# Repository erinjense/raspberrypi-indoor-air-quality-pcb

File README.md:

# zephyrus-iaq
Hardware and Software for an Indoor Air Quality Logger

More to come...

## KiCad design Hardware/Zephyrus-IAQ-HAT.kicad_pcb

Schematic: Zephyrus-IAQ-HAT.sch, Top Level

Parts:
J1: Conn_02x20_Odd_Even__Rpi; PinSocket_2x20_P2.54mm_Vertical
J2: USART; JST_SM04B-SRSS-TB(LF)(SN)
R9, R20: 10k; R_0805_2012Metric
U3: BSS138

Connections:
+3V3: J1.1, J1.17, R20.1, U3.G; also elsewhere on the board
+5V: J2.4 (VCC), R9.1; also elsewhere on the board
/FAN_PWM1: J1.33; also elsewhere on the board
/FAN_nSLEEP: J1.22; also elsewhere on the board
/GPIO2(SDA1): J1.3; also elsewhere on the board
/GPIO3(SCL1): J1.5; also elsewhere on the board
/GPIO4(GCLK): J1.7
/GPIO5: J1.29
/GPIO6: J1.31
/GPIO7(SPI1_CE_N): J1.26
/GPIO8(SPI0_CE_N): J1.24
/GPIO9(SPI0_MISO): J1.21
/GPIO10(SPI0_MOSI): J1.19
/GPIO11(SPI0_SCK): J1.23
/GPIO12(PWM0): J1.32
/GPIO14(TXD0): J1.8, J2.1 (TX)
/GPIO15(RXD0): J1.10, R20.2, U3.S
/GPIO16: J1.36
/GPIO17(GEN0): J1.11; also elsewhere on the board
/GPIO18(GEN1)(PWM0): J1.12; also elsewhere on the board
/GPIO19(SPI1_MISO): J1.35
/GPIO20(SPI1_MOSI): J1.38
/GPIO21(SPI1_SCK): J1.40
/GPIO22(GEN3): J1.15; also elsewhere on the board
/GPIO23(GEN4): J1.16
/GPIO24(GEN5): J1.18
/GPIO26: J1.37
/GPIO27(GEN2): J1.13; also elsewhere on the board
/ID_SC_EEPROM: J1.28; also elsewhere on the board
/ID_SD_EEPROM: J1.27; also elsewhere on the board
/RXD0: J2.2 (RX), R9.2, U3.D
GND: J1.6, J1.9, J1.14, J1.20, J1.25, J1.30, J1.34, J1.39, J2.3 (GND); also elsewhere on the board

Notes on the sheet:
Power Mgmt.
DAC/Buffer power control for Analog Sensors Analog Sensor Ports: A0-A5
A0 - A5: Analog Channels Buffers (250 [mA] to A0 - A5) DAC (0 - 5 [V] to Buffers)
Unidirectional Fan
6:1 Multiplexed ADC (0 - 5 [V])
3.3V to 5V I2C I2C Connectors
Multiplexed 16-bit ADC
I2C Connectors and I2C Logic Level Conversion
Software Driver: zephyrus-iaq/Software/HAT/IAQ_DAC43608.py zephyrus-iaq/Software/HAT/IAQ_AnalogPortController.py
Software Driver: zephyrus-iaq/Software/HAT/IAQ_Mux.py zephyrus-iaq/Software/third_party/Adafruit_I2C.py zephyrus-iaq/Software/third_party/Adafruit_ADS1x15.py
Raspberry Pi Header
5V USART , 3.3V Pi Compatible
Raspberry Pi HAT Requirements: EEPROM
Mnt. Holes
EEPROM
SCL/SDA 5V is on the same I2C bus as 3.3V SCL/SDA
Step the TX line from target device down for 3.3V RX on Raspbery line Similiar BSS138 circuit as I2C logic level shifting.
Raspberry Pi 3.3V TX can register HIGH on 5V TTL compatible USART
PWM controlled Fan

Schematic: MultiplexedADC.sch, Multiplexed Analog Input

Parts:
C11, C12, C14: 100nF; C_0805_2012Metric
J9: Alert; PinHeader_1x01_P2.54mm_Vertical
R10: 10K; R_0805_2012Metric
U6: MUX; SOP65P640X120-16N
U7: ADC; SOP50P490X110-10N
U8: V-Shift; SOP65P640X120-14N

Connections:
+5V: C11.1, C12.1, C14.1, R10.1, U6.16 (VCC), U7.8 (VDD), U8.14 (VCC); also elsewhere on the board
/ADC0: U6.13 (Y0); also elsewhere on the board
/ADC1: U6.14 (Y1); also elsewhere on the board
/ADC2: U6.15 (Y2); also elsewhere on the board
/ADC3: U6.12 (Y3); also elsewhere on the board
/ADC4: U6.1 (Y4); also elsewhere on the board
/ADC5: U6.5 (Y5); also elsewhere on the board
/GPIO17(GEN0): U8.2 (1A); also elsewhere on the board
/GPIO22(GEN3): U8.9 (3A); also elsewhere on the board
/GPIO27(GEN2): U8.5 (2A); also elsewhere on the board
/Multiplexed ADC/MUL_A_5V: U6.11 (A), U8.3 (1Y)
/Multiplexed ADC/MUL_B_5V: U6.10 (B), U8.6 (2Y)
/Multiplexed ADC/MUL_C_5V: U6.9 (C), U8.8 (3Y)
/SCL_5: U7.1 (ADDR), U7.10 (SCL); also elsewhere on the board
/SDA_5: U7.9 (SDA); also elsewhere on the board
GND: C11.2, C12.2, C14.2, U6.6 (~INH~), U6.7 (GND), U6.8 (GND), U7.3 (GND), U7.5 (AIN1), U7.6 (AIN2), U7.7 (AIN3), U8.1 (1!OE), U8.4 (2!OE), U8.7 (GND), U8.10 (3!OE); also elsewhere on the board
unnamed: J9.1, R10.2, U7.2 (ALERT/RDY)
unnamed: U6.3 (COM), U7.4 (AIN0)

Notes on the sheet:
Multiplexer 6:1 Analog Input to ADC Channels: A0 - A5
ADS1115 16-bit ADC 5 [V] I2C Interface
Software Driver: zephyrus-iaq/Software/third_party/Adafruit_I2C.py zephyrus-iaq/Software/third_party/Adafruit_ADS1x15.py
Software Driver: zephyrus-iaq/Software/HAT/IAQ_Mux.py
Raspberry Pi 3.3 [V] TTL Shifted To Multiplexer 5 [V] CMOS.
Address: 0x4B

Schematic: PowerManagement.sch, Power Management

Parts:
C1, C13: 47uF; C_0805_2012Metric
D1: PWR; D_0805_2012Metric
D10: SMBJ5.0A
F1: MF-MSMF250/X; Fuse_1812_4532Metric
J7: 10103594-0001LF; FCI_10103594-0001LF
R3: 330; R_0805_2012Metric
R4: 2.61k; R_0805_2012Metric
R23: 100k; R_0805_2012Metric
R24: 287; R_0805_2012Metric
U10: 5V; REG_EY1501DI-ADJ

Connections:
+5V: C13.1, R4.1, R23.1, U10.1 (Vout), U10.2 (Vout); also elsewhere on the board
/Power Management/VREG_SENSE: R4.2, R24.1, U10.3 (SENSE)
GND: C1.2, C13.2, D10.2, J7.5, R3.2, R23.2, R24.2, U10.4 (PG), U10.5 (GND), U10.11 (Pad); also elsewhere on the board
unnamed: C1.1, D1.2 (A), D10.1, F1.2, U10.7 (ENABLE), U10.9 (Vin), U10.10 (Vin)
unnamed: D1.1 (K), R3.1
unnamed: F1.1, J7.1

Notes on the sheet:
5V Power: Micro USB Input
5V Regulator (0.125V drop @ 2A)
Polyfuse 2.5A hold ; 5A trip
TVS 5V Reverse 9.2V Clamp Max
The micro-USB power input was inspired by reading the documents on the Raspberry Pi 3 B+ at the following link (Upper Left Hand Corner of Schematic): https://www.raspberrypi.org/documentation/hardware/raspberrypi/schematics/rpi_SCH_3bplus_1p0_reduced.pdf License: https://www.raspberrypi.org/creativ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

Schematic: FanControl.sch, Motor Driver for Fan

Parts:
C3, C4: 100nF; C_0805_2012Metric
J4: Fan; SM02B-SRSS-TB(LF)(SN)
U2: Fan Driver; SON50P200X200X80-9N

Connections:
+3V3: C4.1, U2.8 (VCC); also elsewhere on the board
+5V: C3.1, U2.1 (VM); also elsewhere on the board
/FAN_PWM1: U2.6 (IN1); also elsewhere on the board
/FAN_nSLEEP: U2.7 (nSLEEP); also elsewhere on the board
GND: C3.2, C4.2, U2.4 (GND), U2.5 (IN2), U2.9 (Thermal); also elsewhere on the board
unnamed: J4.1, U2.2 (OUT1)
unnamed: J4.2, U2.3 (OUT2)

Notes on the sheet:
2-Pin Connector for Fan (Unidirectional Control)

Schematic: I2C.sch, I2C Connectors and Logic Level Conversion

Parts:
J6, J8: I2C 3.3V; JST_SM04B-SRSS-TB(LF)(SN)
J16: I2C 5V; JST_SM04B-SRSS-TB(LF)(SN)
J17: PPS; PinSocket_1x01_P2.54mm_Vertical
R16, R17: 10k; R_0805_2012Metric
U4, U5: BSS138

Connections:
+3V3: J6.2 (VDD), J8.2 (VDD), U4.G, U5.G; also elsewhere on the board
+5V: J16.2 (VDD), R16.1, R17.1; also elsewhere on the board
/GPIO2(SDA1): J6.3 (SDA), J8.3 (SDA), U4.S; also elsewhere on the board
/GPIO3(SCL1): J6.4 (SCL), J8.4 (SCL), U5.S; also elsewhere on the board
/GPIO18(GEN1)(PWM0): J17.1; also elsewhere on the board
/SCL_5: J16.4 (SCL), R17.2, U5.D; also elsewhere on the board
/SDA_5: J16.3 (SDA), R16.2, U4.D; also elsewhere on the board
GND: J6.1 (GND), J8.1 (GND), J16.1 (GND); also elsewhere on the board

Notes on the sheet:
3.3V I2C Connectors Compatible with Sparkfun's Qwiic system.
Pulse Per Second Breakout for Sparkfun GPS
3.3V and 5V I2C Connectors
The Bi-Directional logic level shift using the BSS138 was inspired by reading Sparkfun's schematic https://cdn.sparkfun.com/datasheets/BreakoutBoards/Logic_Level_Bidirectional.pdf License: https://creativecommons.org/licenses/by-sa/3.0/us/ Changes: There is no Pull-Up on the Source, because of the 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

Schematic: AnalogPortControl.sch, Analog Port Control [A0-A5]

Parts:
C5, C6, C7, C9: 100nF; C_0805_2012Metric
C8, C10: 10uF; C_0805_2012Metric
D4, D5, D6, D7, D8, D9: LED; D_0805_2012Metric
J10: A0; JST_SM03B-SRSS-TB(LF)(SN)
J11: A1; JST_SM03B-SRSS-TB(LF)(SN)
J12: A2; JST_SM03B-SRSS-TB(LF)(SN)
J13: A3; JST_SM03B-SRSS-TB(LF)(SN)
J14: A4; JST_SM03B-SRSS-TB(LF)(SN)
J15: A5; JST_SM03B-SRSS-TB(LF)(SN)
R11, R12, R14, R15, R18, R19: 330; R_0805_2012Metric
R13: 10k; R_0805_2012Metric
U9: DAC; QFN50P300X300X80-17N
U11: Buffer; SOP65P640X120-14N
U12: Buffer; SOP65P490X110-8N

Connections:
+5V: C5.1, C6.1, C7.1, C8.1, C9.1, C10.1, R13.1, U9.13 (VDD), U9.15 (Vref), U11.4 (V+), U12.8 (V+); also elsewhere on the board
/ADC0: J10.3; also elsewhere on the board
/ADC1: J11.3; also elsewhere on the board
/ADC2: J12.3; also elsewhere on the board
/ADC3: J13.3; also elsewhere on the board
/ADC4: J14.3; also elsewhere on the board
/ADC5: J15.3; also elsewhere on the board
/Analog Port Control/BUF_OUT_0: J10.1, R11.2, U11.6 (-InB), U11.7 (OutB)
/Analog Port Control/BUF_OUT_1: J11.1, R12.2, U11.1 (OutA), U11.2 (-InA)
/Analog Port Control/BUF_OUT_2: J12.1, R14.2, U11.8 (OutC), U11.9 (-InC)
/Analog Port Control/BUF_OUT_3: J13.1, R15.2, U11.13 (-InD), U11.14 (OutD)
/Analog Port Control/BUF_OUT_4: J14.1, R18.2, U12.1 (OUTA), U12.2 (-INA)
/Analog Port Control/BUF_OUT_5: J15.1, R19.2, U12.6 (-INB), U12.7 (OUTB)
/Analog Port Control/DAC_OUT_A: U9.1 (VoutA), U11.5 (+InB)
/Analog Port Control/DAC_OUT_B: U9.2 (VoutB), U11.3 (+InA)
/Analog Port Control/DAC_OUT_C: U9.3 (VoutC), U11.10 (+InC)
/Analog Port Control/DAC_OUT_D: U9.4 (VoutD), U11.12 (+InD)
/Analog Port Control/DAC_OUT_E: U9.9 (VoutE), U12.5 (+INB)
/Analog Port Control/DAC_OUT_F: U9.10 (VoutF), U12.3 (+INA)
/SCL_5: U9.6 (SCL); also elsewhere on the board
/SDA_5: U9.5 (SDA), U9.7 (AO); also elsewhere on the board
GND: C5.2, C6.2, C7.2, C8.2, C9.2, C10.2, D4.1 (K), D5.1 (K), D6.1 (K), D7.1 (K), D8.1 (K), D9.1 (K), J10.2, J11.2, J12.2, J13.2, J14.2, J15.2, U9.8 (~LDAC~), U9.14 (Agnd), U9.17 (Thermal), U11.11 (V-), U12.4 (V-); also elsewhere on the board
unnamed: D4.2 (A), R11.1
unnamed: D5.2 (A), R12.1
unnamed: D6.2 (A), R14.1
unnamed: D7.2 (A), R15.1
unnamed: D8.2 (A), R18.1
unnamed: D9.2 (A), R19.1
unnamed: R13.2, U9.16 (~CLR~)

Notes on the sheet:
Analog Connector Ports [A0 - A5] (MQ Gas Sesnors) 0 - 5 [V] from DAC Up to 250 mA from Buffers
Buffers Up to 250 mA per channel Single Supply
I2C Address: 0x4A ~LDAC~=0 is asynchronous mode (immediate update on DAC after write to register)
DAC43608 Digital to Analog Converter (8-bit) Allows 0 to 5 V power control for Analog channels A0 to A5
AD8532: Op Amp
~CLR~ always high. A logic low clears the DAC buffers to zero.
Software Driver: zephyrus-iaq/Software/HAT/IAQ_DAC43608.py
AD8534: Op Amp

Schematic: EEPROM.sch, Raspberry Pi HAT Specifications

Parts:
C2: 100nF; C_0805_2012Metric
J3: Jumper; PinSocket_1x02_P2.54mm_Vertical
R1: 1k; R_0805_2012Metric_Pad1.15x1.40mm_HandSolder
R2: DNP; R_0805_2012Metric_Pad1.15x1.40mm_HandSolder
R5, R6: 3.9k; R_0805_2012Metric_Pad1.15x1.40mm_HandSolder
U1: EEPROM; SOIC127P600X175-8N

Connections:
+3V3: C2.1, R1.1, R5.1, R6.1, U1.8 (VCC); also elsewhere on the board
/ID_SC_EEPROM: R6.2, U1.6 (SCL); also elsewhere on the board
/ID_SD_EEPROM: R5.2, U1.5 (SDA); also elsewhere on the board
GND: C2.2, J3.2, R2.1, U1.1 (A0), U1.2 (A1), U1.3 (A2), U1.4 (VSS); also elsewhere on the board
unnamed: J3.1, R1.2, R2.2, U1.7 (WP)

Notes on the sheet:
At boot time this I2C interface will be interrogated to look for an EEPROM that identifes the attached board and allows automagic setup of the GPIOs (and optionally, Linux drivers).
EEPROM

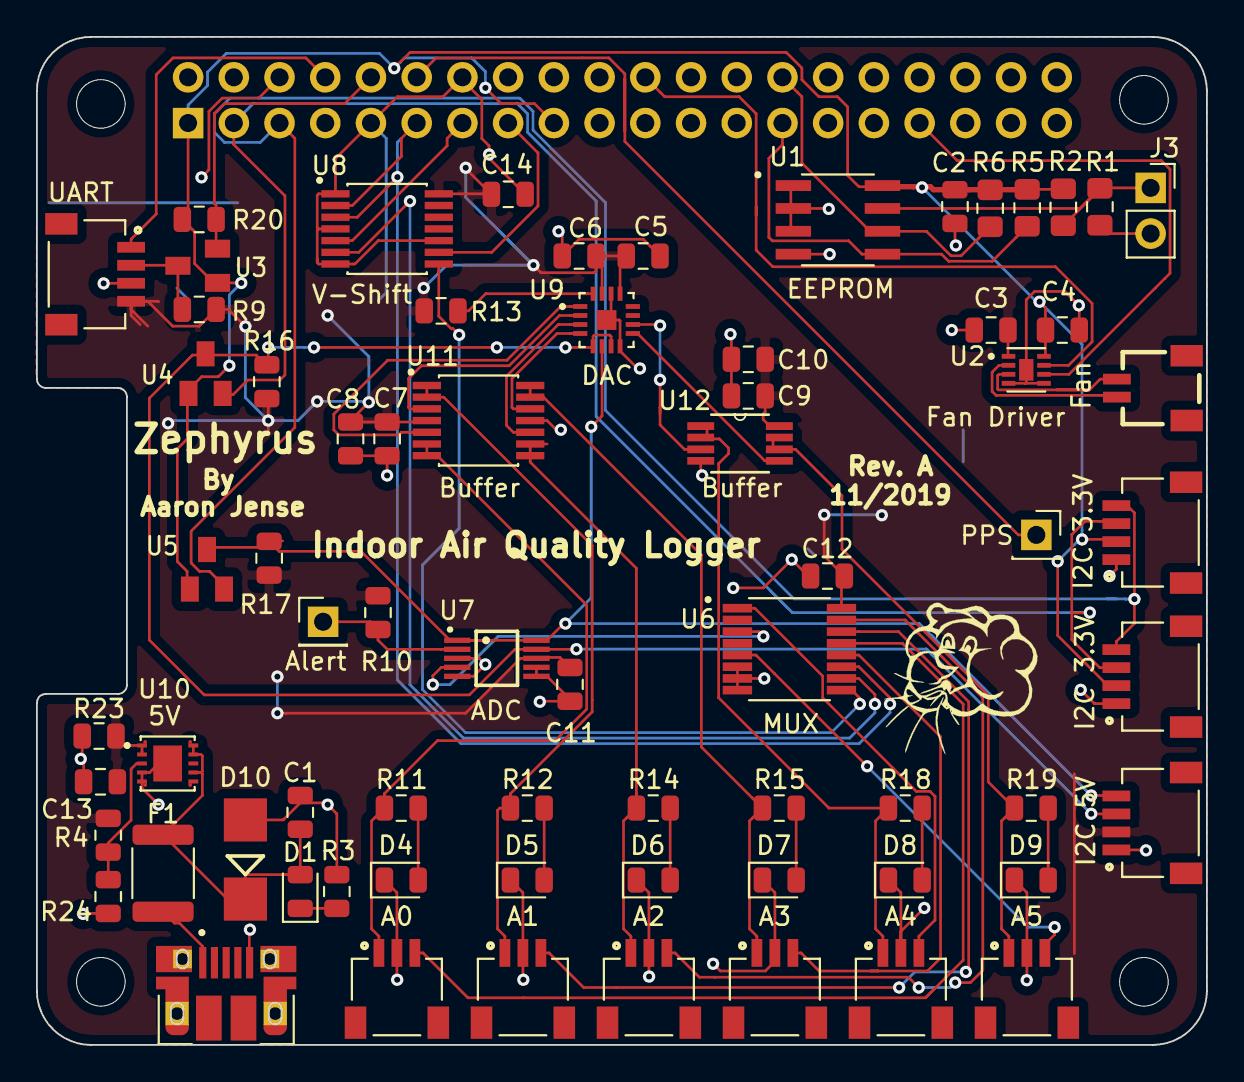
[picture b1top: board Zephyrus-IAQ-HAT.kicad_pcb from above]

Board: 2 copper layers, 65.0 x 56.0 mm, 75 parts (1 on the bottom side), 55 nets.

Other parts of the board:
MK1, MK2, MK3, MK4: M2.5; MountingHole_2.7mm_M2.5

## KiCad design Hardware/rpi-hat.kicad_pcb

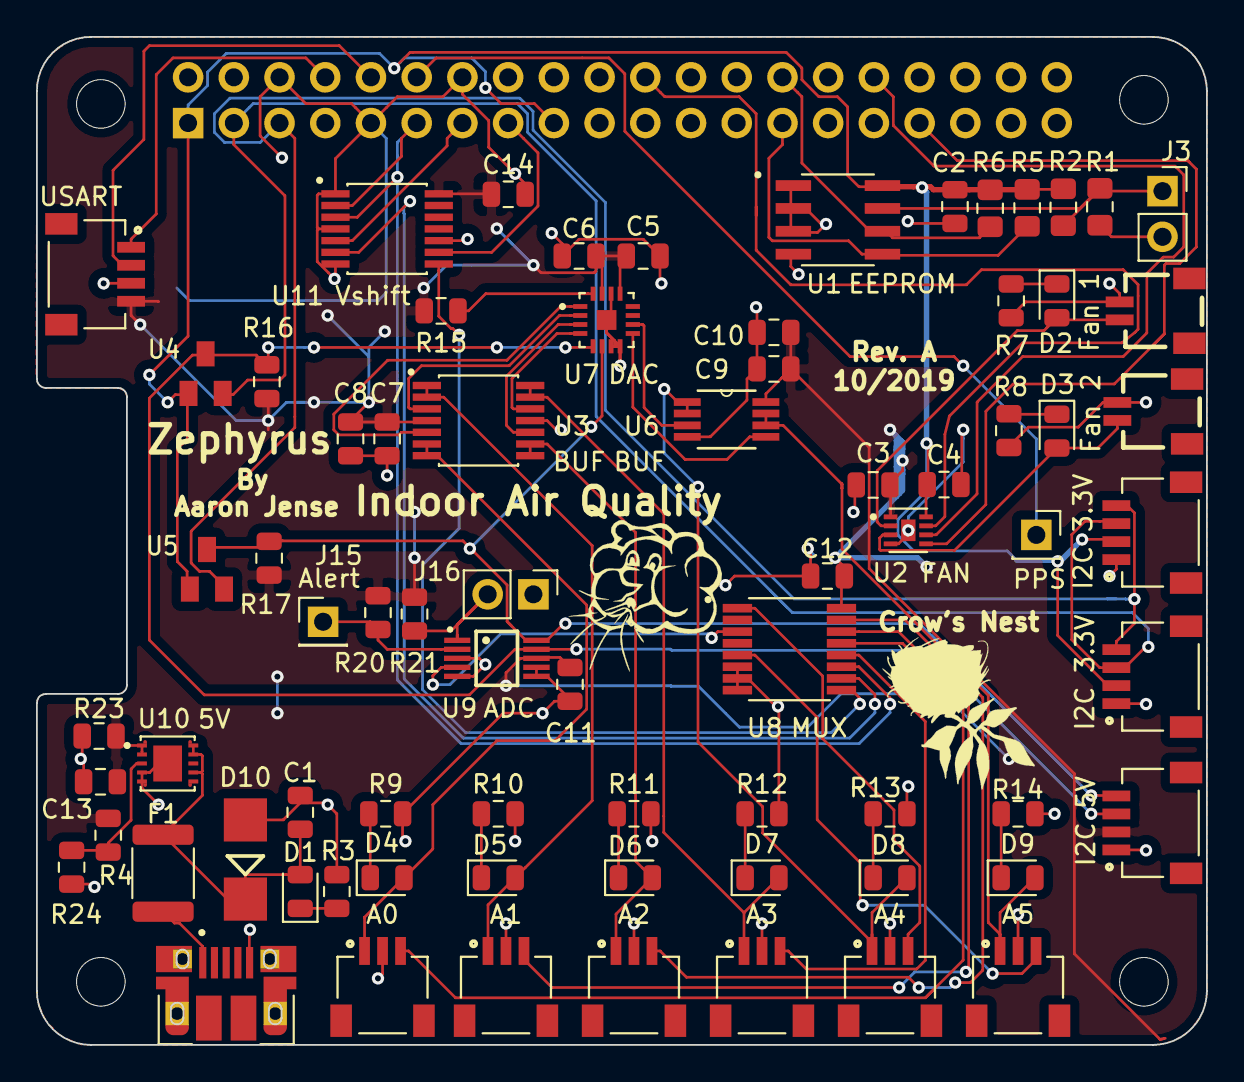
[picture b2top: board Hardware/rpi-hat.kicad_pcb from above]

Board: 2 copper layers, 65.0 x 56.0 mm, 79 parts (1 on the bottom side), 58 nets.

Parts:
C1, C13: 47uF; C_0805_2012Metric
C2, C3, C4, C5, C6, C7, C9, C11, C12, C14: 100nF; C_0805_2012Metric
C8, C10: 10uF; C_0805_2012Metric
D1: PWR; D_0805_2012Metric
D2, D3, D4, D5, D6, D7, D8, D9: LED; D_0805_2012Metric
D10: SMBJ5.0A
F1: MF-MSMF250/X; Fuse_1812_4532Metric
J1: Conn_02x20_Odd_Even__Rpi; PinSocket_2x20_P2.54mm_Vertical
J2: USART; JST_SM04B-SRSS-TB(LF)(SN)
J3: Jumper; PinSocket_1x02_P2.54mm_Vertical
J4: Fan 1; SM02B-SRSS-TB(LF)(SN)
J5: Fan 2; SM02B-SRSS-TB(LF)(SN)
J6, J8: I2C 3.3V; JST_SM04B-SRSS-TB(LF)(SN)
J7: 10103594-0001LF; FCI_10103594-0001LF
J9: A0; JST_SM03B-SRSS-TB(LF)(SN)
J10: A1; JST_SM03B-SRSS-TB(LF)(SN)
J11: A2; JST_SM03B-SRSS-TB(LF)(SN)
J12: A3; JST_SM03B-SRSS-TB(LF)(SN)
J13: A4; JST_SM03B-SRSS-TB(LF)(SN)
J14: A5; JST_SM03B-SRSS-TB(LF)(SN)
J15: Alert; PinHeader_1x01_P2.54mm_Vertical
J16: I2C 5V; JST_SM04B-SRSS-TB(LF)(SN)
J16#2: Conn_01x02_Male; PinHeader_1x02_P2.54mm_Vertical
J17: PPS; PinSocket_1x01_P2.54mm_Vertical
MK1, MK2, MK3, MK4: M2.5; MountingHole_2.7mm_M2.5
R1: 1k; R_0805_2012Metric_Pad1.15x1.40mm_HandSolder
R2: DNP; R_0805_2012Metric_Pad1.15x1.40mm_HandSolder
R3, R7, R8, R9, R10, R11, R12, R13, R14: 330; R_0805_2012Metric
R4: 2.61k; R_0805_2012Metric
R5, R6: 3.9k; R_0805_2012Metric_Pad1.15x1.40mm_HandSolder
R15: 10k; R_0805_2012Metric
R16, R17: 3.3k; R_0805_2012Metric
R20, R21: 10K; R_0805_2012Metric
R23: 100k; R_0805_2012Metric
R24: 287; R_0805_2012Metric
U1: EEPROM; SOIC127P600X175-8N
U2: FAN; SON50P200X200X80-9N
U3: BUF; SOP65P640X120-14N
U4, U5: BSS138
U6: BUF; SOP65P490X110-8N
U7: DAC; QFN50P300X300X80-17N
U8: MUX; SOP65P640X120-16N
U9: ADC; SOP50P490X110-10N
U10: 5V; REG_EY1501DI-ADJ
U11: Vshift; SOP65P640X120-14N

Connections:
+3V3: C2.1, C4.1, J1.1, J1.17, J6.2, J8.2, R1.1, R5.1, R6.1, U1.8, U2.8, U4.G, U5.G
+5V: C3.1, C5.1, C6.1, C7.1, C8.1, C9.1, C10.1, C11.1, C12.1, C13.1, C14.1, J2.4, J16.2, R4.1, R15.1, R16.1, R17.1, R20.1, R21.1, R23.1, U2.1, U3.4, U6.8, U7.13, U7.15, U8.16, U9.8, U10.1, U10.2, U11.14
/ADC0: J9.3, U8.13
/ADC1: J10.3, U8.14
/ADC2: J11.3, U8.15
/ADC3: J12.3, U8.12
/ADC4: J13.3, U8.1
/ADC5: J14.3, U8.5
/ADC_Subsystem/ADC_ADDR: J16#2.2, R21.2, U9.1
/ADC_Subsystem/ADC_ALERT: J15.1, R20.2, U9.2
/ADC_Subsystem/MUL_A_5V: U8.11, U11.3
/ADC_Subsystem/MUL_B_5V: U8.10, U11.6
/ADC_Subsystem/MUL_COM: U8.3, U9.4
/ADC_Subsystem/MUL_C_5V: U8.9, U11.8
/Analog_Sensors/BUF_OUT_0: D4.2, J9.1, U3.6, U3.7
/Analog_Sensors/BUF_OUT_1: D5.2, J10.1, U3.1, U3.2
/Analog_Sensors/BUF_OUT_2: D6.2, J11.1, U3.8, U3.9
/Analog_Sensors/BUF_OUT_3: D7.2, J12.1, U3.13, U3.14
/Analog_Sensors/BUF_OUT_4: D8.2, J13.1, U6.1, U6.2
/Analog_Sensors/BUF_OUT_5: D9.2, J14.1, U6.6, U6.7
/Analog_Sensors/DAC_CLR: R15.2, U7.16
/Analog_Sensors/DAC_OUT_A: U3.5, U7.1
/Analog_Sensors/DAC_OUT_B: U3.3, U7.2
/Analog_Sensors/DAC_OUT_C: U3.10, U7.3
/Analog_Sensors/DAC_OUT_D: U3.12, U7.4
/Analog_Sensors/DAC_OUT_E: U6.5, U7.9
/Analog_Sensors/DAC_OUT_F: U6.3, U7.10
/FAN_PWM0: J1.32, U2.6
/FAN_PWM1: J1.33, U2.5
/FAN_nSLEEP: J1.22, U2.7
/Fan_Control/FAN_OUT1: D2.2, J4.1, U2.2
/Fan_Control/FAN_OUT2: D3.2, J5.1, U2.3
/GPIO2(SDA1): J1.3, J6.3, J8.3, U4.S
/GPIO3(SCL1): J1.5, J6.4, J8.4, U5.S
/GPIO14(TXD0): J1.8, J2.1
/GPIO15(RXD0): J1.10, J2.2
/GPIO17(GEN0): J1.11, U11.2
/GPIO18(GEN1)(PWM0): J1.12, J17.1
/GPIO22(GEN3): J1.15, U11.9
/GPIO27(GEN2): J1.13, U11.5
/ID_SC_EEPROM: J1.28, R6.2, U1.6
/ID_SD_EEPROM: J1.27, R5.2, U1.5
/PowerManagement/VREG_IN_5V: C1.1, D1.2, D10.1, F1.2, U10.7, U10.9, U10.10
/PowerManagement/VREG_SENSE: R4.2, R24.1, U10.3
/SCL_5: J16.4, R17.2, U5.D, U7.6, U9.10
/SDA_5: J16.3, R16.2, U4.D, U7.5, U9.9
GND: C1.2, C2.2, C3.2, C4.2, C5.2, C6.2, C7.2, C8.2, C9.2, C10.2, C11.2, C12.2, C13.2, C14.2, D10.2, J1.6, J1.9, J1.14, J1.20, J1.25, J1.30, J1.34, J1.39, J2.3, J3.2, J4.2, J5.2, J6.1, J7.5, J8.1, J9.2, J10.2, J11.2, J12.2, J13.2, J14.2, J16.1, J16#2.1, R2.1, R3.2, R7.2, R8.2, R9.2, R10.2, R11.2, R12.2, R13.2, R14.2, R23.2, R24.2, U1.1, U1.2, U1.3, U1.4, U2.4, U2.9, U3.11, U6.4, U7.7, U7.8, U7.14, U7.17, U8.6, U8.7, U8.8, U9.3, U9.5, U9.6, U9.7, U10.4, U10.5, U10.11, U11.1, U11.4, U11.7, U11.10
unnamed: D1.1, R3.1
unnamed: D2.1, R7.1
unnamed: D3.1, R8.1
unnamed: D4.1, R9.1
unnamed: D5.1, R10.1
unnamed: D6.1, R11.1
unnamed: D7.1, R12.1
unnamed: D8.1, R13.1
unnamed: D9.1, R14.1
unnamed: F1.1, J7.1
unnamed: J3.1, R1.2, R2.2, U1.7

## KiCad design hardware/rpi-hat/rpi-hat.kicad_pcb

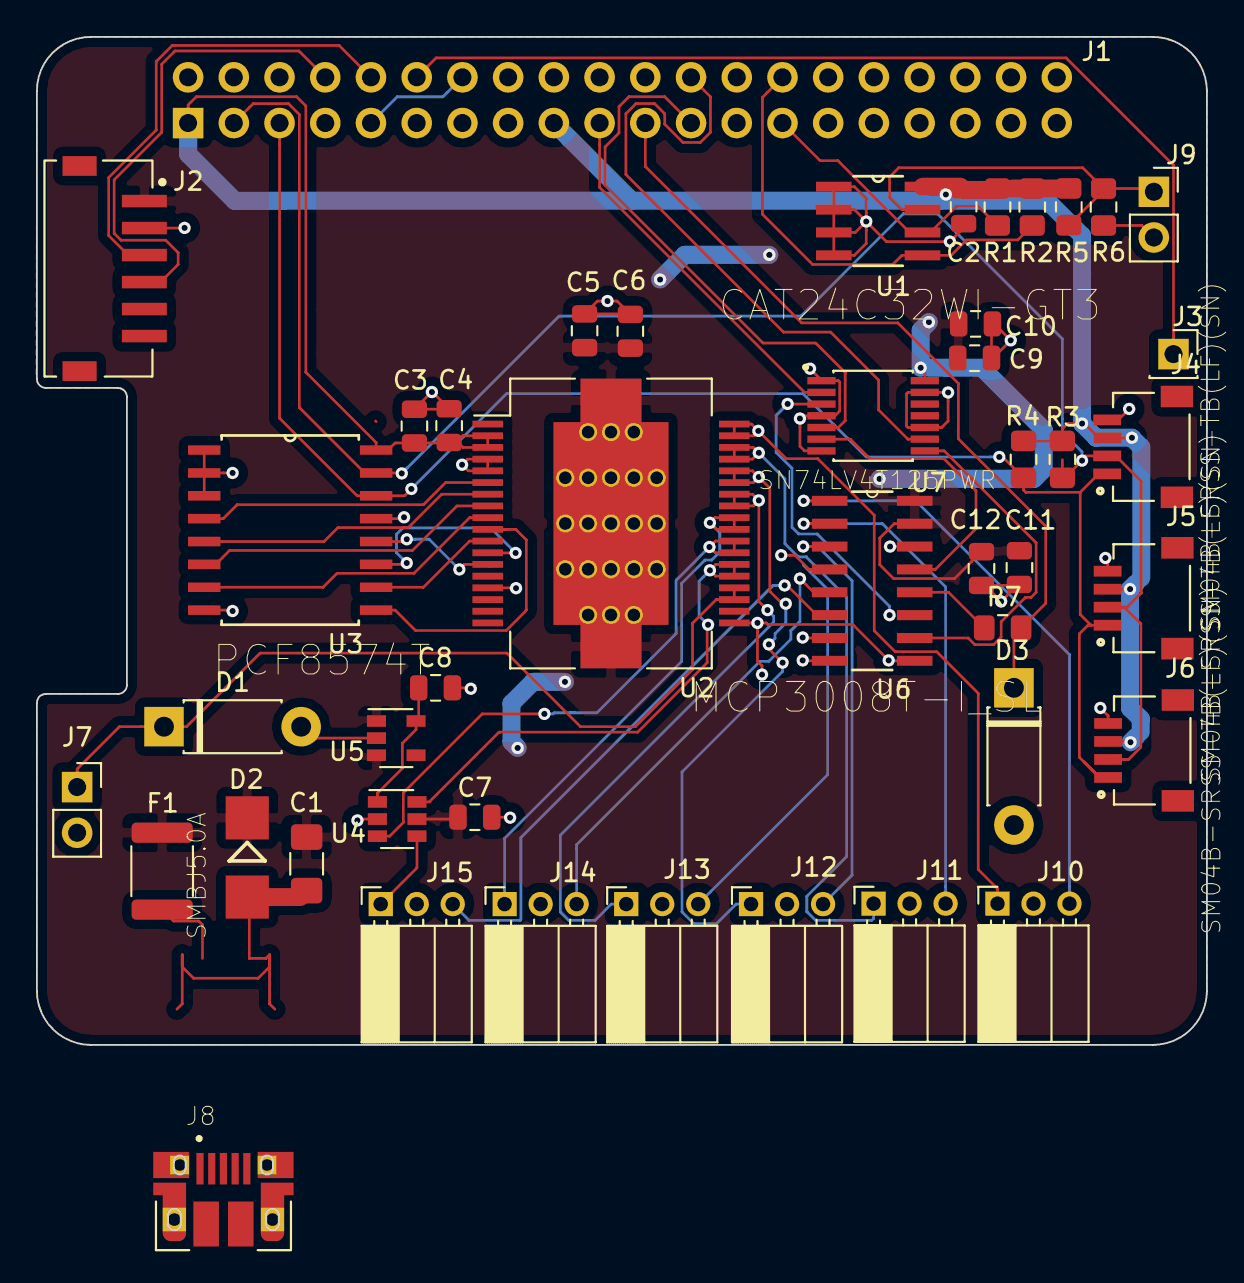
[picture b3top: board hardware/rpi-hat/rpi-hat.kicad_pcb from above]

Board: 2 copper layers, 65.0 x 56.0 mm, 49 parts (1 on the bottom side), 44 nets.

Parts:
C1: 47uF; R_1206_3216Metric_Pad1.42x1.75mm_HandSolder
C2, C3, C4, C5, C9, C12: 100nF; C_0805_2012Metric
C6: 47uF; C_0805_2012Metric
C7, C8: 1uF; C_0805_2012Metric
C10, C11: 10uF; C_0805_2012Metric
D1: D_Zener; D_DO-41_SOD81_P7.62mm_Horizontal
D2: SMBJ5.0A
D3: 1N4728A_3.3V_100uA; D_DO-41_SOD81_P7.62mm_Horizontal
F1: MF-MSMF250/X; Fuse_1812_4532Metric
J1: Conn_02x20_Odd_Even__Rpi; PinSocket_2x20_P2.54mm_Vertical
J2: JST_S6B-ZR-SM4A-TF(LF)(SN)
J3: Conn_01x01_Female; PinSocket_1x01_P2.54mm_Vertical
J4, J5, J6: SM04B-SRSS-TB(LF)(SN); JST_SM04B-SRSS-TB(LF)(SN)
J7: Conn_01x02_Female; PinSocket_1x02_P2.54mm_Vertical
J8: 10103594-0001LF; FCI_10103594-0001LF
J9: Conn_01x02_Male; PinSocket_1x02_P2.54mm_Vertical
J10, J11, J12, J13, J14, J15: Conn_MQ_Gas; PinSocket_1x03_P2.00mm_Horizontal
MK1, MK2, MK3, MK4: M2.5; MountingHole_2.7mm_M2.5
R1, R2: 3.9k; R_0805_2012Metric_Pad1.15x1.40mm_HandSolder
R3, R4, R5: 10k; R_0805_2012Metric_Pad1.15x1.40mm_HandSolder
R6: DNP; R_0805_2012Metric_Pad1.15x1.40mm_HandSolder
R7: 270; R_0805_2012Metric_Pad1.15x1.40mm_HandSolder
U1: CAT24C32WI-GT3; SOIC127P600X175-8N
U2: ISO1H811G; HSOP-36-1EP_11.0x15.9mm_P0.65mm_SlugDown_ThermalVias
U3: PCF8574T; SOIC127P1032X265-16N
U4: SN74LVC1G3157; SOT-23-6
U5: NCP699; SOT-23-5
U6: MCP3008T-I_SL; SOIC127P600X175-16N
U7: SN74LV4T125PWR; SOP65P640X120-14N

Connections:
+3V3: C2.1, C3.1, C4.1, J1.1, J1.17, J4.3, J5.3, J6.3, R1.1, R2.1, R3.1, R4.1, R5.1, U1.8, U2.2, U2.3, U3.16
+5V: C1.1, C5.1, C6.1, C7.1, C9.1, C10.1, C11.1, C12.1, D2.1, F1.1, J2.1, U2.37, U4.5, U5.1, U5.3, U6.15, U6.16, U7.14
/ADC0: J10.3, U6.1
/ADC1: J11.3, U6.2
/ADC2: J12.3, U6.3
/ADC3: J13.3, U6.4
/ADC4: J14.3, U6.5
/ADC5: J15.3, U6.6
/ADC_Subsystem/MOSI_5: U6.11, U7.3
/ADC_Subsystem/SCK_5: U6.13, U7.6
/ADC_Subsystem/~CE~_5: U6.10, U7.8
/Analog_Sensors/1V4: C8.1, U4.1, U5.5
/Analog_Sensors/5V_1V4_0V: J15.1, U4.4
/Analog_Sensors/D0: U2.6, U3.4
/Analog_Sensors/D1: U2.7, U3.5
/Analog_Sensors/D2: U2.8, U3.6
/Analog_Sensors/D3: U2.9, U3.7
/Analog_Sensors/D4: U2.10, U3.9
/Analog_Sensors/D5: U2.11, U3.10
/Analog_Sensors/D6: U2.12, U3.11
/Analog_Sensors/D7: U2.13, U3.12
/Analog_Sensors/Vswitch0: J10.1, U2.35, U2.36
/Analog_Sensors/Vswitch1: J11.1, U2.33, U2.34
/Analog_Sensors/Vswitch2: J12.1, U2.31, U2.32
/Analog_Sensors/Vswitch3: J13.1, U2.29, U2.30
/Analog_Sensors/Vswitch4: J14.1, U2.27, U2.28
/Analog_Sensors/Vswitch5: U2.25, U2.26, U4.3
/Analog_Sensors/Vswitch6: U2.23, U2.24, U4.6
/GPIO8(SPI0_CE_N): J1.24, U7.9
/GPIO9(SPI0_MISO): D3.1, J1.21, R7.2
/GPIO10(SPI0_MOSI): J1.19, U7.2
/GPIO11(SPI0_SCK): J1.23, U7.5
/ID_SC_EEPROM: J1.28, R2.2, U1.5
/Vfan: D1.1, J7.1, U2.21, U2.22
GND: C1.2, C2.2, C3.2, C4.2, C5.2, C6.2, C7.2, C8.2, C9.2, C10.2, C11.2, C12.2, D1.2, D2.2, D3.2, J1.6, J1.9, J1.14, J1.20, J1.25, J1.30, J1.34, J1.39, J2.2, J4.4, J5.4, J6.4, J7.2, J8.5, J8.S3, J8.S4, J8.S5, J8.S6, J9.2, J10.2, J11.2, J12.2, J13.2, J14.2, J15.2, R6.1, U1.1, U1.2, U1.3, U1.4, U2.4, U2.5, U2.15, U2.19, U3.1, U3.2, U3.3, U3.8, U3.13, U4.2, U5.2, U6.9, U6.14, U7.1, U7.4, U7.7, U7.10, U7.13
GPS_PPS: J1.12, J3.1
ID_SD_EEPROM: J1.27, R1.2, U1.6
unnamed: F1.2, J8.1
unnamed: J9.1, R5.2, R6.2, U1.7
unnamed: R7.1, U6.12
RXD0: J1.10, J2.3
SCL: J1.5, J4.1, J5.1, J6.1, R4.2, U3.14
SDA: J1.3, J4.2, J5.2, J6.2, R3.2, U3.15
TXD0: J1.8, J2.4

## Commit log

2019-03-20 Initial Commit. Basic CSV test.
2019-03-22 Csv object can now be initialized with various other csv files
2019-03-22 Allow test configuration csv to be tracked for now
2019-03-31 Simplified configuration
2019-04-13 Add Telaire 6004 CO2 Symbol for KiCad
2019-04-13 Initial KiCad Schematic/Layout for Raspberry Pi Breakout. EEPROM added later for Hat spec.
2019-04-13 Temporary libraries until Raspberry Pi Breakout Template parts are updated.
2019-04-13 Add KiCad Symbol for Qwiic GPS
2019-04-13 Add KiCad Symbol for Sharp GP2Y1010.
2019-04-20 Most functionality added. EEPROM for HAT spec, various JST connectors for sensors, ADC subsystem and power subsystem
2019-04-21 Begin layout
2019-10-01 New HAT features.
2019-10-01 Update lib
2019-10-01 Update footprint library
2019-10-01 Clean Up KiCad Library
2019-10-01 KiCad Library Cleanup.
2019-10-02 DRC passing changes. Proper pin identifiers.
    Need to swap SN74LVC1G3157 for a power multiplexor IC.
2019-10-02 Documentation
2019-10-07 Update Schematic/Layout
2019-10-07 Update KiCad Layout
2019-10-07 KiCad Layout Update
2019-10-07 PCB Complete. Pending Review.
2019-10-09 Add Voltage Regulator. Update traces.
2019-10-09 Update PCB Logo
2019-10-09 Fixed EEPROM I2C. Removed uneeded pull up resistors.
    Rpi has internal pull ups.
2019-10-10 Added Level Shifter for Multiplexer
2019-10-14 Updated Schematic and Layout
    Created a schematic sheet for each subsystem.
    Fixed INH on MUX being wrongly tied to an enable pin.
    INH: GND (Always output Y0-Y5/A0-A5 on MUX)
    Fixed SDA/SCL mix-up on 3.3V I2C Connector.
2019-10-14 Schematic Cleanup
2019-10-15 Update I2C netlist and footprint association
2019-10-15 Update Footprint association for EEPROM
2019-10-15 Fix EEPROM SD and SC lines
2019-10-17 TODO: Config, DAC43608, FileHandler
2019-10-17 Add Adafruit I2C code
2019-10-18 Update PCB
2019-10-20 Change Buffer footprint.
2019-10-20 Update silk screen
2019-10-20 Update I2C Documentation
2019-10-22 Remove pull-up resistor for outdated multiplexor INH
2019-10-22 Hardware changes for PCB order 1
2019-10-22 Reorganized directory layout
2019-10-22 Initial GUI Commit
2019-10-22 Add MQ gas sensor reading test app
2019-10-28 Add functionality for MQ Gas Sensors
2019-10-31 Update GUIV2.py
    This is the newer version
2019-11-03 Project Directory Formatting
2019-11-03 Change IAQ_CSV.py to IAQ_FileHandler.py
2019-11-03 Simplify StartPage
2019-11-03 Change GUIV2.py to IAQ_GUI.py and changed it's demo behavior
2019-11-03 Add Button naming from list
2019-11-03 Simplify sensor frames into one SensorView Class
2019-11-03 Simplify the GUI output API
2019-11-03 Add Logger class to IAQ_Logger Update Config files Change some name schemes
2019-11-03 Update Logger setup routine
2019-11-04 SDS011 Particulate Sensor Initial Code
2019-11-04 Add IAQ_Sensor.py
2019-11-04 Update Multiplexer and Analog Port Controller
2019-11-04 Created IAQ_MqGas
2019-11-05 Add Custom Exceptions and directory hierarchy
2019-11-05 Connected MqGas Sensors from inside Logger to AnalogPortController.
2019-11-05 Update file permissions
2019-11-05 Change how to call IAQ_Logger.py
2019-11-05 SystemInfo user input simplified and working
2019-11-06 Add exceptions for when no sensors are connected.
2019-11-10 Rudimentry SQLite Support Support for creating a default SQLite database The database contains a Sensors table with setup info. for each MQ gas sensor. The database contains a data storage table for 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
2019-11-10 Select MQ Sensors can now log their data to their own database
2019-11-10 Added Port:Sensor dictionary to keep track of which sensors are on or off
2019-11-10 Add features for GUI and AnalogPortController GUI won't create SensorView for sensors that are turned off GUI will rename default button names from [A0-A5] to their assigned sensor or keep default if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
2019-11-11 Update GUI. Groundwork for having multiple sensor views depending if sensor is setup or not.
2019-11-12 GUI Features Created StartPage update for each analog button name and color
2019-11-12 Changed how the portStatus dictionary is created from the sensor setup database GUI is now initialized based off of the portStatus dictionary from database and not hard-coded values
2019-11-14 Rudimentry user input for GUI.
2019-11-14 Initial BME680 temp/humidity integration into logging
2019-11-16 Organized Schematic Naming and Added Comments
2019-11-16 Organized schematic naming
2019-11-18 Up Changed I2C addres for DAC and ADC. Added MOSFET to USART RX.
2019-11-18 Removed unecessary files
2019-11-19 Updated Schematic Attribution and Documentation
2019-11-19 Updated schematic library location
2019-11-19 Exported Schematic as PDF
2019-11-19 Add Pull-Up to UART line.
2019-11-19 Begin GUI Overhaul. Changed GUI button names, and general layout
2019-11-19 Update PCB to latest schematic changes.
2019-11-20 Update footprint for AD8532, traces, and back silkscreen.
2019-11-21 Fix fan control.
2019-11-23 Add dedicated USB Port setup script
2019-11-23 Rudimentry USB storage support.
2019-11-24 Rudimentry data to CSV support
2019-11-24 Add GUI buttons for turning logger On/Off and mounting/ejecting USB
2019-11-24 Rudimentry CO2 and GPS Support
2019-11-24 Match /dev/disk/by-path to Raspberry Pi 3 B+ (was Raspberry Pi 3 B)
2019-11-25 Integration of USB mount/eject with GUI
2019-11-25 Fix usb-port-setup.sh to use udev rules symlink
2019-11-25 Add CSV logging to IAQ_Logger
2019-11-25 Simplify checking if USB is attached
2019-11-26 Cleanup GUI
2019-11-27 Simplify sensor setup, add SCD30, BME680 and SDS011 to CSV logging
2019-11-27 Add GUI time update (polling based)
2019-11-27 Change timers in IAQ_LOGGER
2019-11-28 Add formatted data output for each sensor to GUI. Change ADC gain.
2019-11-28 Add Settings Button
2019-11-29 Architecture update
2019-11-29 Changes for sensor setup edge cases
2019-11-29 Update Settings view, and options. Added back-icon.png when in settings menu
2019-11-30 Update Setup Scripts
2019-12-01 Fix bugs: 1.) IAQ_Config: Moved Humidity and Pressure locations to match data order. 2.) usb-port-setup.sh: Made sure to chown /media/zephyrus-iaq-usb for pi. 3.) IAQ_BME680: Except IOError from I2C.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
2019-12-01 Update README image
2019-12-03 Add last two analog ports to AnalogPortController. Add SDS011 read error.
2019-12-03 Update setup scripts to allow normal user to shutdown/reboot
2019-12-03 Rudimentry shutdown/reboot support for GUI.
2019-12-04 Add 3D footprints from SnapEDA
    Hardware/Pictures are Creative Commons.
    KiCad schematic symbols, 2D footprints, and 3D footprints from SnapEDA or KiCad Library.
2019-12-04 AD8532ARMZ Footprint change.
2019-12-04 Add On/Off status to sensor config. Changed SDS011 units
2019-12-04 Update CO2 and GPS functionality.
2019-12-05 Crontab script
2019-12-05 Update GUI to fullscreen
2019-12-09 Update naming and units.
